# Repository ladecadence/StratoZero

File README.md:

# StratoZero

StratoZero is a Raspberry Pi Zero hat for use in High Altitude Balloon missions.
It uses a RFM95 LoRa radio module, ds18b20 temperature sensors, a mcp3002 SPI ADC to monitor the battery, a MS5607 barometer, and several connectors for GPS, I2C, analog inputs, and more.

Check BOM File for components.

This board is designed to be used with the EkiGo flight software: [https://github.com/ladecadence/EkiGo](https://github.com/ladecadence/EkiGo)

## Component changes

 * Initial tests with the original voltage regulator showed brownouts, so now I'm using an MIC39100-5 and it works perfect (same footprint).
 * DS3231 and it's battery come from the small and cheap RTC modules you can find on ebay or aliexpress.

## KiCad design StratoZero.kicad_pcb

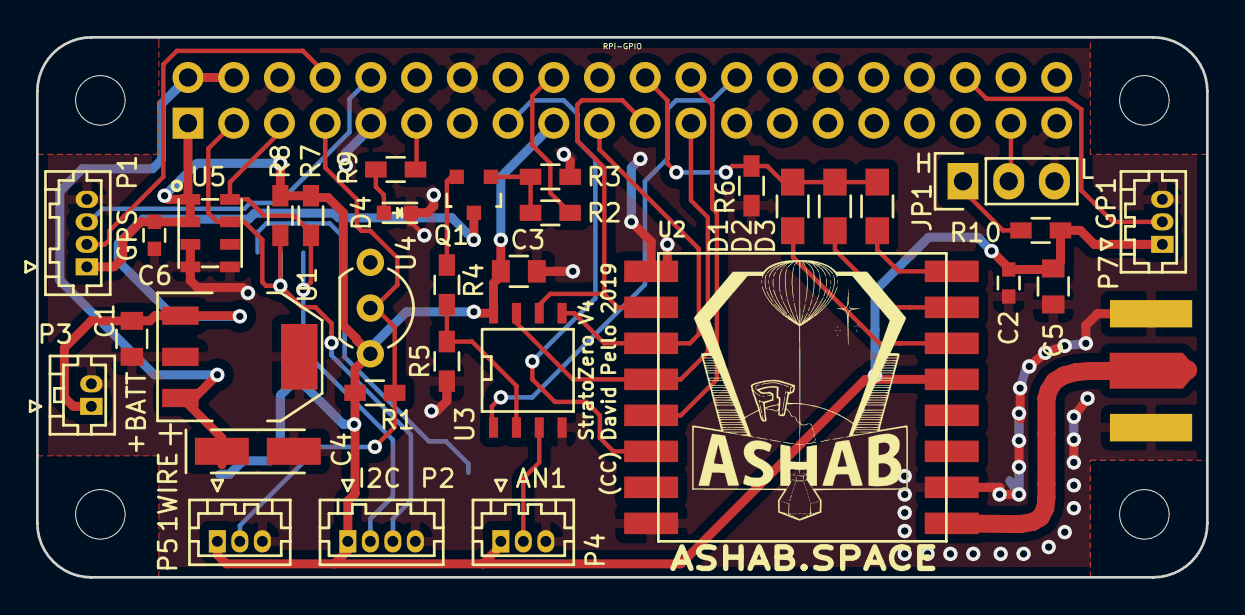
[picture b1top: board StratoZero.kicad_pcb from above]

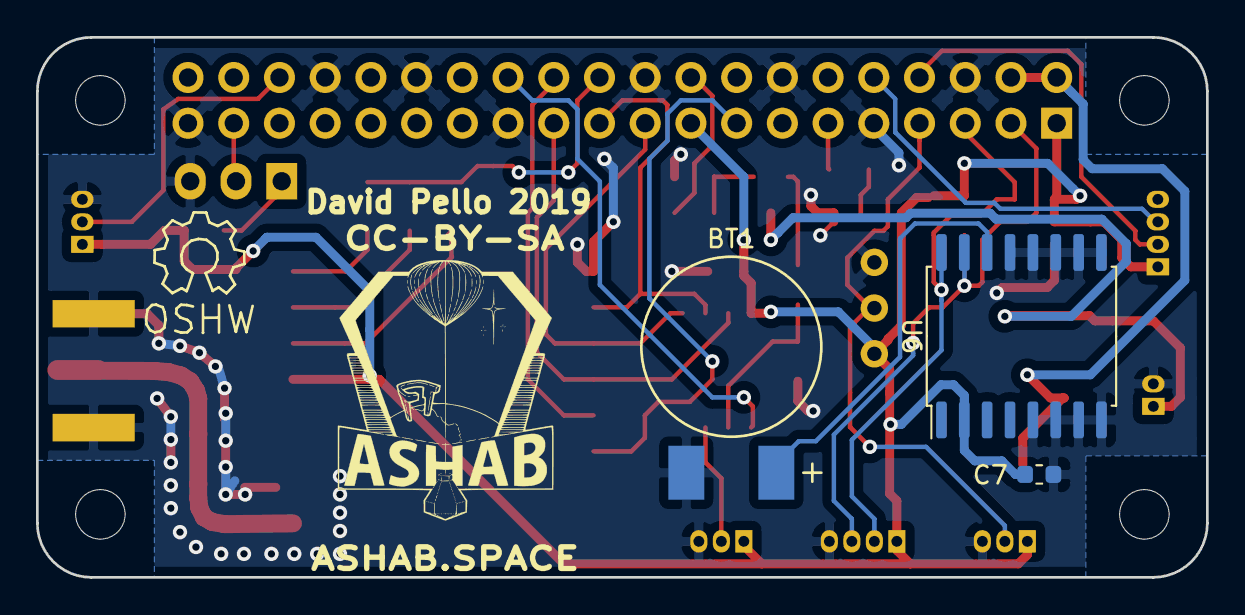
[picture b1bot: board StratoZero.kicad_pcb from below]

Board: 2 copper layers, 65.0 x 30.0 mm, 38 parts (3 on the bottom side), 31 nets.

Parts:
BT1: Battery_Cell; RTC-Batt
C1: 470n; C_0805
C2, C6: 100n; C_0603
C3: 100n; C_0805
C4: CP; TantalC_SizeA_EIA-3216_HandSoldering
C5: 1u; C_0805
C7: 100n; C_0603_1608Metric
D1, D2, D3: D; R_0805_HandSoldering
D4: LED; LED_0603
JP1: RF_PWR; Pin_Header_Straight_1x03
P1: GPS; Hirose_DF13-04P-1.25DSA_04x1.25mm_Straight
P2: I2C; Hirose_DF13-04P-1.25DSA_04x1.25mm_Straight
P3: BATT; Hirose_DF13-02P-1.25DSA_02x1.25mm_Straight
P4: AN1; Hirose_DF13-03P-1.25DSA_03x1.25mm_Straight
P5: 1WIRE; Hirose_DF13-03P-1.25DSA_03x1.25mm_Straight
P6: RPI-GPIO; RPI-ZERO-Hat
P7: GP1; Hirose_DF13-03P-1.25DSA_03x1.25mm_Straight
Q1: 2N7002; SOT-23
R1: 4K7R; R_0603_HandSoldering
R2: 100R; R_0603_HandSoldering
R3, R5, R6, R7, R8, R10: 10K; R_0603_HandSoldering
R4: 22K; R_0603_HandSoldering
R9: 390; R_0603_HandSoldering
SMA_E1: SMA_EDGE
U1: LM2940; SOT-223
U2: RFM95HW; RFM95_SMD_Handsoldering
U3: MCP3002; SOIC-8-N
U4: ds18b20; TO-92_Inline_Wide
U5: MS5607
U6: DS3231M; SOIC-16W_7.5x10.3mm_P1.27mm

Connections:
1WIRE: P5.2, P6.7, R1.2, U4.2
+3V3: C2.1, C3.1, C5.1, C6.1, C7.1, P1.1, P2.1, P4.1, P5.1, P6.1, P6.17, P7.1, R1.1, R7.1, R8.1, R10.2, U2.13, U3.8, U4.3, U5.1, U5.2, U6.2
+5V: C4.1, P6.2, P6.4, U1.3
+BATT: C1.1, P3.1, Q1.3, U1.1
/RF: SMA_E1.1, U2.9
AN1: P4.2, U3.3
CS0: P6.24, U2.5
CS1: P6.26, U3.1
EXT_GPIO: P6.36, P7.2
GND: BT1.2, C1.2, C2.2, C3.2, C4.2, C5.2, C6.2, C7.2, D4.1, JP1.3, P1.4, P2.4, P3.2, P4.3, P5.3, P6.6, P6.9, P6.14, P6.20, P6.25, P6.30, P6.34, P6.39, P7.3, R3.2, R5.2, R6.2, SMA_E1.0, SMA_E1.2, U1.2, U1.4, U2.1, U2.8, U2.10, U3.4, U4.1, U5.3, U5.4, U5.5, U6.5, U6.6, U6.7, U6.8, U6.9, U6.10, U6.11, U6.12, U6.13
LED: P6.11, R9.2
LORA_INT: D1.1, D2.1, D3.1, P6.22, R6.1
LORA_RST: P6.15, U2.6
MISO: P6.21, U2.2, U3.6
MOSI: P6.19, U2.3, U3.5
unnamed: D1.2, U2.14
unnamed: D2.2, U2.15
unnamed: D3.2, U2.16
unnamed: D4.2, R9.1
unnamed: JP1.1, R10.1
unnamed: Q1.1, R2.1, R3.1
unnamed: Q1.2, R4.1
unnamed: R4.2, R5.1, U3.2
READ_BATT_EN: P6.18, R2.2
RXD: P1.3, P6.10
SCL: P2.2, P6.5, R7.2, U5.8, U6.16
SCLK: P6.23, U2.4, U3.7
SDA: P2.3, P6.3, R8.2, U5.7, U6.15
TXD: P1.2, P6.8
TX_PWR: JP1.2, P6.37
VMEM: BT1.1, U6.14

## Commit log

2017-05-15 initial import, v0.2, RF power jumper
2017-05-15 Description
2017-05-26 Improved RF Path
2019-10-08 Updated to V4, minor fixes and new RTC and battery on board
2025-05-21 Update README.md with software link

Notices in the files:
StratoZero.kicad_pcb:
CC-BY-SA
